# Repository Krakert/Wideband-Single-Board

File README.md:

# Wideband-Single-Board
This is a redesigned pcb, based on the work of [mck1117](https://github.com/mck1117 "mck1117").
For the original design see [this repo.](https://github.com/mck1117/wideband)

# changes to the board
* just a 2 layer board instead of 4.
* Used of a more commonly available main connector [MX23A12NF1](https://www.jae.com/en/connectors/series/detail/product/id=64755&type_code=T1040), 
can be found on [Aliexpress](https://www.aliexpress.com/item/1005001800960426.html?af=1844390_1&cv=28981226&cn=42qyelwgsm8ikhj5hl6txnks2aob1h19&dp=v5_42qyelwgsm8ikhj5hl6txnks2aob1h19&utm_source=epn&utm_medium=cpa&utm_campaign=1844390_1&utm_content=28981226&product_id=1005001800960426&afref=&aff_fcid=90c424390c0e4096a8f60ebfebd85c97-1629909089116-07017-_bXFaygG&tt=API&aff_fsk=_bXFaygG&aff_platform=api-new-link-generate&sk=_bXFaygG&aff_trace_key=90c424390c0e4096a8f60ebfebd85c97-1629909089116-07017-_bXFaygG&terminal_id=aba9bb32104148aea4404679ecf2bd02).

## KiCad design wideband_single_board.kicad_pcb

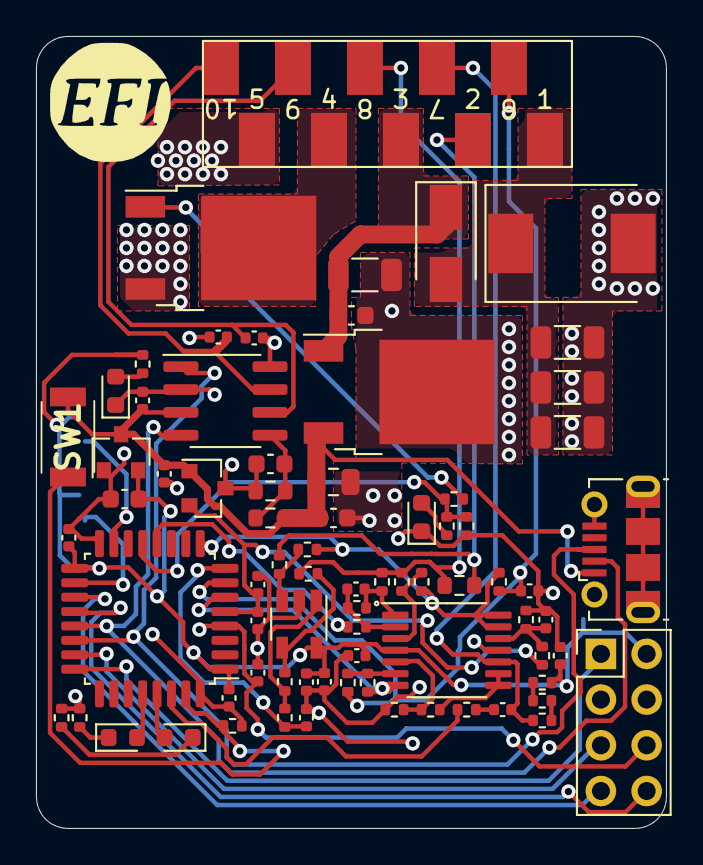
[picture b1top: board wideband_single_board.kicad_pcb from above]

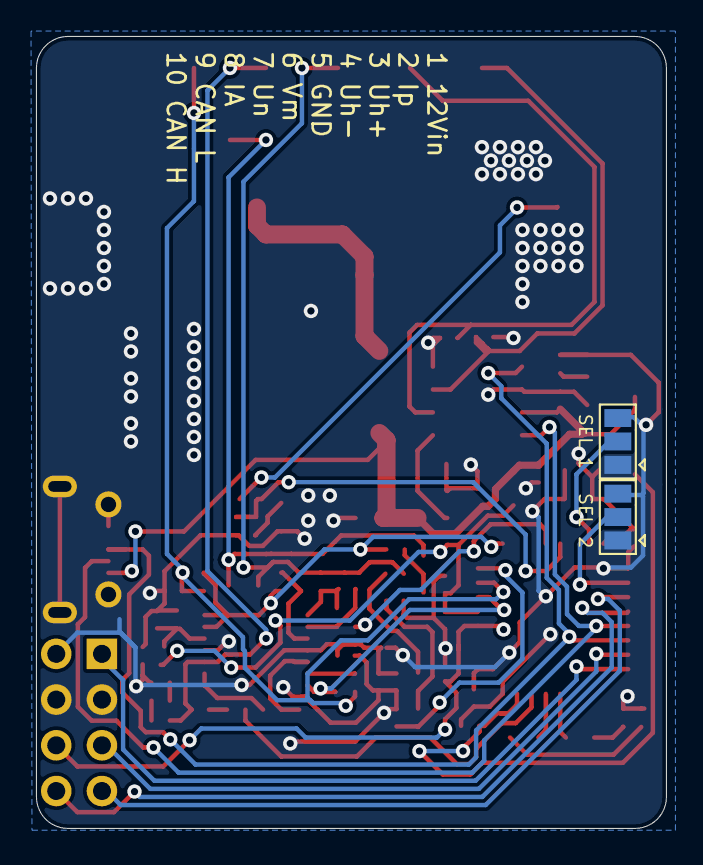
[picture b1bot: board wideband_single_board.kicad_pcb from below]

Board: 2 copper layers, 35.0 x 44.0 mm, 79 parts (2 on the bottom side), 50 nets.

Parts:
C1, C8, C16, C17, C21: 1u; C_0402_1005Metric
C2, C12, C14, C20, C22, C23, C24, C26: 100n; C_0402_1005Metric
C3, C6, C7, C9: 10u; C_1206_3216Metric
C4: 4.7u; C_0603_1608Metric
C5: 33n; C_0402_1005Metric
C10, C11, C15: 1u; C_0603_1608Metric
C13: 22u; C_0805_2012Metric
C18, C19: 47p; C_0402_1005Metric
C25, C27: DNP; C_0402_1005Metric
D1: D_TVS; D_SMC
D2, D6: RED; LED_0603_1608Metric
D3: D_Schottky; D_SMA
D4: BLUE; LED_0603_1608Metric
D5: GREEN; LED_0603_1608Metric
G?: LOGO
J1: Conn_02x05_Top_Bottom; Solder_pad_5X2X3.0X2.0mm
J2: USB_B_Micro; USB_Micro-B_Molex-105017-0001
J3: Conn_02x04_Top_Bottom; PinHeader_2x04_P2.54mm_Vertical
JP1, JP2: Jumper_3_Open; SolderJumper-3_P1.3mm_Open_Pad1.0x1.5mm
Q1: BTS3028; TO-252-2
R1, R2, R9, R26, R27, R29, R30, R31: 1k; R_0402_1005Metric
R3, R4: 68k; R_0402_1005Metric
R5, R6, R11, R12, R15, R16, R28: 10k; R_0402_1005Metric
R7: 10; R_0402_1005Metric
R8: 47; R_0402_1005Metric
R10: 61.9; R_0603_1608Metric
R13, R14: 100k; R_0402_1005Metric
R17, R20: 27k; R_0402_1005Metric
R18: 22k; R_0402_1005Metric
R19: 3.3k; R_0402_1005Metric
R21, R22, R25: 20k; R_0402_1005Metric
R23: 220; R_0603_1608Metric
R24: 470; R_0603_1608Metric
SW1: SW_Push; TS1088R02026
U1: XC6206P332MR; SOT-23
U2: MCP6004; TSSOP-14_4.4x5mm_P0.65mm
U3: LM78M05_TO252; TO-252-2
U4: AD8628; TSOT-23-5
U5: TJA1051T-3; SOIC-8_3.9x4.9mm_P1.27mm
U6: REF3033; SOT-23
U7: STM32F042K6Tx; LQFP-32_7x7mm_P0.8mm

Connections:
12V_RAW: C3.1, C6.2, C7.1, D1.1, D3.2, J1.1
+3V3: C4.1, C22.1, C23.1, C24.1, C25.1, C26.1, C27.1, J3.2, JP1.3, JP2.3, R9.2, R25.1, U1.2, U2.4, U4.5, U7.1, U7.17
+5V: C2.1, C11.1, C13.1, C16.1, J2.1, R23.1, SW1.2, U1.3, U3.3, U5.3, U6.1
/Boot0: R28.2, SW1.1, U7.31
/CAN_H: C18.2, J1.10, U5.7
/CAN_L: C19.1, J1.9, U5.6
/CAN_RX: J2.2, U5.4, U7.21
/CAN_TX: J2.3, U5.1, U7.22
/Ip_dac: R3.1, U7.12
/Ip_sense: C14.1, R19.2, U7.8
/LED_BLUE: D4.2, U7.28
/LED_GREEN: D5.2, U7.29
/LSU_Heater+: C9.1, C10.1, D3.1, J1.3, U3.1
/LSU_Heater-: J1.4, Q1.2
/LSU_Ip: J1.2, R10.2, R12.2
/LSU_Rtrim: J1.8, R6.1, R8.1, R10.1, R11.2
/LSU_Un: C12.1, J1.7, R21.1, U2.10
/LSU_Un_sense: R16.1, U2.8, U2.9
/LSU_Vm: C8.1, J1.6, R7.1, R15.1, U7.7
/Nernst_esr_drive: R18.1, U7.30
/SEL_1: JP1.2, U7.15
/SEL_2: JP2.2, U7.18
/SWCLK: J3.1, U7.24
/SWDIO: J3.5, U7.23
/UART_RX: J3.8, U7.20
/UART_TX: J3.7, U7.19
/Un_sense: R20.2, U2.7, U7.6
/Vm: R4.2, R7.2, R13.2, U2.13, U2.14, U7.9
/heater_pwm: R29.2, R30.2, R31.2, U7.13
/nRESET: C21.1, J3.6, U7.4
GND: C1.2, C2.2, C3.2, C4.2, C6.1, C7.2, C8.2, C9.2, C10.2, C11.2, C13.2, C14.2, C15.2, C16.2, C17.2, C18.1, C19.2, C20.2, C21.2, C22.2, C23.2, C24.2, C25.2, C26.2, C27.2, D1.2, D2.1, D6.1, J1.5, J2.5, J2.6, J3.3, J3.4, JP1.1, JP2.1, Q1.3, R2.2, R17.2, R24.2, R26.1, R27.1, R28.1, R30.1, U1.1, U2.11, U3.2, U4.2, U5.2, U5.8, U6.3, U7.16, U7.32
unnamed: C1.1, R1.2, R2.1, U2.12
unnamed: C5.1, R5.1, R8.2, U2.1
unnamed: C5.2, R3.2, R5.2, U2.2
unnamed: C12.2, R18.2
unnamed: C15.1, R23.2, R24.1, U5.5
unnamed: D2.2, R9.1
unnamed: D4.1, R26.2
unnamed: D5.1, R27.2
unnamed: D6.2, R29.1
unnamed: Q1.1, R31.1
unnamed: R4.1, R6.2, U2.3
unnamed: R11.1, R14.2, U4.4
unnamed: R12.1, R13.1, U4.3
unnamed: R14.1, R19.1, U4.1
unnamed: R15.2, R20.1, U2.6
unnamed: R16.2, R17.1, U2.5
unnamed: R21.2, R22.2
unnamed: R22.1, R25.2
VDDA: C17.1, C20.1, R1.1, U6.2, U7.5

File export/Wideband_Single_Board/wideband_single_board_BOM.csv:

Comment,Designator,Footprint,LCSC
"1u","C10,C11,C15","Capacitor_SMD:C_0603_1608Metric","C15849"
"22u","C13","Capacitor_SMD:C_0805_2012Metric","C45783"
"100n","C2,C12,C14,C20,C22,C23,C24,C26","Capacitor_SMD:C_0402_1005Metric","C1525"
"47p","C18,C19","Capacitor_SMD:C_0402_1005Metric","C1567"
"1u","C1,C8,C16,C17,C21","Capacitor_SMD:C_0402_1005Metric","C52923"
"DNP","C25,C27","Capacitor_SMD:C_0402_1005Metric",""
"10u","C3,C6,C7,C9","Capacitor_SMD:C_1206_3216Metric","C13585"
"4.7u","C4","Capacitor_SMD:C_0603_1608Metric","C19666"
"33n","C5","Capacitor_SMD:C_0402_1005Metric","C1585"
"D_TVS","D1","Diode_SMD:D_SMC","C151279"
"RED","D2,D6","LED_SMD:LED_0603_1608Metric","C2286"
"D_Schottky","D3","Diode_SMD:D_SMA","C22452"
"BLUE","D4","LED_SMD:LED_0603_1608Metric","C72041"
"GREEN","D5","LED_SMD:LED_0603_1608Metric","C72043"
"Conn_02x05_Top_Bottom","J1","TestPoint:Solder_pad_5X2X3.0X2.0mm",""
"USB_B_Micro","J2","Connector_USB:USB_Micro-B_Molex-105017-0001","C404969"
"Conn_02x04_Top_Bottom","J3","Connector_PinHeader_2.54mm:PinHeader_2x04_P2.54mm_Vertical",""
"Jumper_3_Open","JP1,JP2","Jumper:SolderJumper-3_P1.3mm_Open_Pad1.0x1.5mm",""
"BTS3028","Q1","Package_TO_SOT_SMD:TO-252-2","C112639"
"61.9","R10","Resistor_SMD:R_0603_1608Metric","C23092"
"100k","R13,R14","Resistor_SMD:R_0402_1005Metric","C25741"
"22k","R18","Resistor_SMD:R_0402_1005Metric","C25768"
"3.3k","R19","Resistor_SMD:R_0402_1005Metric","C25890"
"27k","R17,R20","Resistor_SMD:R_0402_1005Metric","C25771"
"20k","R21,R22,R25","Resistor_SMD:R_0402_1005Metric","C25765"
"220","R23","Resistor_SMD:R_0603_1608Metric","C22962"
"470","R24","Resistor_SMD:R_0603_1608Metric","C23179"
"1k","R1,R2,R9,R26,R27,R29,R30,R31","Resistor_SMD:R_0402_1005Metric","C11702"
"10k","R5,R6,R11,R12,R15,R16,R28","Resistor_SMD:R_0402_1005Metric","C25744"
"68k","R3,R4","Resistor_SMD:R_0402_1005Metric","C36871"
"10","R7","Resistor_SMD:R_0402_1005Metric","C25077"
"47","R8","Resistor_SMD:R_0402_1005Metric","C25118"
"SW_Push","SW1","lib_wideband_sigle_board:TS1088R02026","C720477"
"XC6206P332MR","U1","Package_TO_SOT_SMD:SOT-23","C5446"
"MCP6004","U2","Package_SO:TSSOP-14_4.4x5mm_P0.65mm","C50282"
"LM78M05_TO252","U3","Package_TO_SOT_SMD:TO-252-2","C58069"
"AD8628","U4","Package_TO_SOT_SMD:TSOT-23-5","C29309"
"TJA1051T-3","U5","Package_SO:SOIC-8_3.9x4.9mm_P1.27mm","C38695"
"REF3033","U6","Package_TO_SOT_SMD:SOT-23","C36658"
"STM32F042K6Tx","U7","Package_QFP:LQFP-32_7x7mm_P0.8mm","C69216"

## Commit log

2021-08-25 first init kicad files
2021-08-25 rename project
2021-08-27 changed overall layout of the board and made a connector board to wire up two LSU4.9 to 2 board in a single case
